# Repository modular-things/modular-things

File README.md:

# Softening Hardware with Modular-Things

use *virtualization* to easily write programs that run across multiple hardware devices

The Modular-Things project is an approach to building modular hardware systems which can be composed in software.
The underlying technology is a small networking library for packetizing and routing messages across devices ([OSAP](http://osap.tools/)) and a [web-based editor](https://modular-things.com/) for composing that hardware into functional systems in software. 

Stated simply our tools let you take hardware devices and add a library to them which allows you to plug that device into a browser-based editor where you can write programs that control it and other devices. Because it's JavaScript in the browser you can also write interfaces in HTML/CSS/JS and import various high-level libraries which interact with and control your physical computing system.

For a succinct introduction (3 min) check out our video for CHI2023 by clicking below.

An example Modular Things construction kit can be seen below with [circuits available here](https://github.com/modular-things/modular-things-circuits).

# Project Background

Modular-Things is written by [Quentin Bolsee](https://github.com/qbolsee), [Leo McElroy](https://github.com/leomcelroy) and [Jake Read](https://github.com/jakeread) based on ongoing work at the [MIT Center for Bits and Atoms](https://cba.mit.edu/) and [Hack Club](https://hackclub.com/). 

It is based on the [surprising performance of modern USB](log/2022-11_usb-motion-perf-tests-log.md), an insight that we picked up from the [urumbu project](https://gitlab.cba.mit.edu/neilg/urumbu) ([paper](https://cba.mit.edu/docs/papers/22.11.Urumbu.pdf)). Under the hood, it uses [osap](http://osap.tools/) to route packets and serialize data. Also inspired by the [virtual-machine](https://cba.mit.edu/docs/theses/16.08.Peek.pdf) architecture pioneered by [Nadya Peek](http://infosyncratic.nl/) and [Ilan Moyer](https://web.mit.edu/imoyer/www/index.html), way back in the way back. 

# Installation and Usage 

You can use the latest modular-things by navigating to [https://modular-things.com/](https://modular-things.com/), or follow these instructions to run it locally:

* install [node.js](https://nodejs.org/en/) - please use version 16.15.1 or above
* clone this repo
* run `npm install` within this repo
* run `npm run dev` to startup a local server !

### Loading Local Files

...modular-things/?file=yourFile.js&panel=devices&panelWidth=70

where file is at `repo/examples/`

--- 

# Writing New Modular-Things

For embedded (arduino) codes, install the OSAP library, which you can download as a zip here: https://github.com/jakeread/osap-arduino, and should also be available via arduino's library manager.

Also, install the `FlashStorage_SAMD` library, via the library manager.

We use the [ArduinoCore-fab-sam](https://github.com/qbolsee/ArduinoCore-fab-sam) for [these circuits](https://github.com/modular-things/modular-things-circuits), which you can install into Arduino via the notes in that repo. For the RP2040 XIAO boards, we use [Earle F. Philhower, the Third's PICO build](https://github.com/earlephilhower/arduino-pico), and for D21 XIAOs, you can follow [the XIAO docs](https://wiki.seeedstudio.com/Seeeduino-XIAO/). 

## Using the Automatic RPC

As of [`osap 0.5.0`](https://github.com/jakeread/osap-arduino/releases/tag/0.5.0), we can use an [improved design pattern](https://ekswhyzee.com/2024/02/09/no-more-newline.html) to build devices. At this time, this will only work on RP2040 based devices (which use a more modern compiler), but it is possible to back port this to c++11 based devices (most Arduinos). 

The basic pattern is pretty simple, we have a function:

```cpp
// types include float, String, int, and boolean 
float someFunction(String oneArgument, int anotherArgument){
  // ... your function body 
}
```

And we include it as a method in the devices' software object with this one-liner, handing it the function poniter, and the names of the function and its arguments: 

```cpp
OSAP_Port_RPC<decltype(&someFunction)> rpcMuleTwo(&someFunction, "someFunction", "oneArgument, anotherArgument");
```

Once we do that, and compile and load the code, the module should appear automatically when it's plugged into modular-things.com/ 

Below is a full example of a device that uses these Automatic RPCs. 

```cpp
#include <osap.h>
#include <Adafruit_GFX.h>
#include <Adafruit_SSD1306.h>

// display setup, which is wired to the XIAO's labelled SCL/SDA pins 
#define SCREEN_WIDTH 128 // OLED display width, in pixels
#define SCREEN_HEIGHT 64 // OLED display height, in pixels
#define SCREEN_ADDRESS 0x3C
Adafruit_SSD1306 display(SCREEN_WIDTH, SCREEN_HEIGHT);

// a potentiometer and a button 
// the pot is on XIAO D2/A2, which is GPIO num 28
// the button is on XIAO D3, which is GPIO num 29 (and will need a pullup)
#define PIN_POTENTIOMETER 28 
#define PIN_BUTTON 29 
#define PIN_LED_BLINK PIN_LED_R 
#define PIN_LED_WD PIN_LED_G 

// we instantiate an OSAP runtime, give it a serialport and a name: 
OSAP_Runtime osap;
OSAP_Gateway_USBSerial serLink(&Serial);
OSAP_Port_DeviceNames namePort("xylo-io-panel");

// now we want to author some functions as interfaces to our device,
// and we'll attach those as RPC's using templated OSAP_Port_RPC<> class instances 

float getPotentiometerReading(void){
  int reading = analogRead(PIN_POTENTIOMETER);
  float duty = (float)reading / 4096.0F;
  return duty; 
}

OSAP_Port_RPC<decltype(&getPotentiometerReading)> getPotRPC(&getPotentiometerReading, "getPotentiometerReading");

bool getButtonState(void){
  // we're not going to debounce anything, 
  // and our button is wired up such that it's logic high when it's not pressed, 
  // so we invert this, 
  return !(digitalRead(PIN_BUTTON));
}

OSAP_Port_RPC<decltype(&getButtonState)> rpcMuleThree(&getButtonState, "getButtonState");

uint32_t blinkOnTime = 0;

void blinkLED(void){
  // we turn an LED on and record the time, 
  // we'll check that in the loop to turn it back off, 
  // note that LEDs are wired such that logic-low is "on"
  digitalWrite(PIN_LED, LOW);
  blinkOnTime = millis();
}

OSAP_Port_RPC<decltype(&blinkLED)> rpcMuleFour(&blinkLED, "blinkLED");

void printToScreen(String message, int textSize){
  display.clearDisplay();
  display.setCursor(0, 0);
  display.setTextSize(textSize);
  display.println(message);
  display.display();
}

OSAP_Port_RPC<decltype(&printToScreen)> rpcMuleTwo(&printToScreen, "printToScreen", "message, textSize");

void newFunctionLiveDemo(int arg){
  printToScreen("you sent..." + String(arg), 3);
}

OSAP_Port_RPC<decltype(&newFunctionLiveDemo)> rpcMuleDemo(&newFunctionLiveDemo, "newFunctionLiveDemo", "intToPrint");

void setup() {
  // setup our LEDs,
  pinMode(PIN_LED_BLINK, OUTPUT);
  pinMode(PIN_LED_WD, OUTPUT);
  digitalWrite(PIN_LED_BLINK, HIGH);

  // the button needs to have a pullup
  pinMode(PIN_BUTTON, INPUT_PULLUP);
  
  // afaik, arduino sets up ADCs just by calling analogRead, 
  // and we also want to set the resolution, 
  analogReadResolution(12);
  int dummy = analogRead(PIN_POTENTIOMETER);

  // we also need to setup the display: 
  display.begin(SSD1306_SWITCHCAPVCC, SCREEN_ADDRESS);
  display.clearDisplay();
  display.display();
  display.setTextColor(SSD1306_WHITE);
  display.setTextWrap(false);

  printToScreen("bonjour", 2);

  // finally, setup OSAP,
  osap.begin();
}

const uint32_t wdInterval = 100;
uint32_t lastWd = 0;

void loop() {
  // osap runs an event loop, 
  osap.loop();

  // and we want to check in on our blinking states, 
  if(blinkOnTime){
    if(blinkOnTime + 250 < millis()){
      blinkOnTime = 0;
      digitalWrite(PIN_LED_BLINK, HIGH);
    }
  }

  // finally, we want to blink the green LED as a watchdog 
  if(lastWd + wdInterval < millis()){
    lastWd = millis();
    digitalWrite(PIN_LED_WD, !digitalRead(PIN_LED_WD));
  }
}
```

## Aligning Two Tiny Programs

To explain how module authorship works, we've just tidied up the `rgbb` example, which you can find [here (arduino)](arduino/rgbb-thing/rgbb-thing.ino) and [here (javascript)](src/lib/virtualThings/rgbb.ts).

Basically: we have an Arduino code that we give a "typeName" - that is then discovered by OSAP via the Modular-Things client. Modular-Things then looks for a matching JS or TS constructor, and if it finds one, instantiates it and passes in the devices' unique name (a string identifier). 

The constructed object can then use that string ID, as well as individual port string IDs, to route messages to its paired object. 

The result is that the "virtual thing" (javascript) acts as a proxy for the arduino-thing, making for cleaner programming model when multiple things exist in the same system. 

<table>
<tr>
  <td>
    <h2><a href="arduino/rgbb-thing/rgbb-thing.ino" target="new">Arduino "RGBB Thing"</a></h2>
  </td>
  <td>
    <h2><a href="src/lib/virtualThings/rgbb.ts" target="new">JavaScript "RGBB Thing"</a></h2>
  </td>
</tr>
<tr>
<td valign="top">

```cpp 
#include <osap.h>

// -------------------------- Define Pins for R,G and B LEDs, and one Button

#define PIN_R 14
#define PIN_G 15
#define PIN_B 16
#define PIN_BUT 17

// -------------------------- Instantiate the OSAP Runtime, 

OSAP_Runtime osap;

// -------------------------- Instantiate a link layer, 
// handing OSAP the built-in Serial object to send packetized 
// data around the network 

OSAP_Gateway_USBSerial serLink(&Serial);

// -------------------------- Adding this software-defined port 
// allows remote services to find the type-name of this device (here "rgbb")
// and to give it a unique name, that will be stored after reset 

OSAP_Port_DeviceNames namePort("rgbb");

// -------------------------- We track button state (in the loop()), 
// and we use the onButtonReq() handler (that we pass into a named port)
// to reply to messages with the provided string-name "getButtonState"

boolean lastButtonState = false;

size_t onButtonReq(uint8_t* data, size_t len, uint8_t* reply){
  // then write-into reply:
  lastButtonState ? reply[0] = 1 : reply[0] = 0;
  return 1;
}

OSAP_Port_Named getButtonState("getButtonState", onButtonReq);

// -------------------------- We can use similar structures without 
// the reply, simply recieving `data, len` on a packet to "setRGB" here 

void onRGBPacket(uint8_t* data, size_t len){
  analogWrite(PIN_R, data[0]);
  analogWrite(PIN_G, data[1]);
  analogWrite(PIN_B, data[2]);
}

OSAP_Port_Named setRGB("setRGB", onRGBPacket);

// -------------------------- Arduino Setup

void setup() {
  // startup the OSAP runtime,
  osap.begin();
  // setup our hardware... 
  analogWriteResolution(8);
  pinMode(PIN_R, OUTPUT);
  pinMode(PIN_G, OUTPUT);
  pinMode(PIN_B, OUTPUT);
  analogWrite(PIN_R, 255);
  analogWrite(PIN_G, 255);
  analogWrite(PIN_B, 255);
  // pull-down switch, high when pressed
  pinMode(PIN_BUT, INPUT);
}

// we debounce the button somewhat 

uint32_t debounceDelay = 10;
uint32_t lastButtonCheck = 0;

// -------------------------- Arduino Loop

void loop() {
  // as often as possible, we want to operate the OSAP runtime, 
  // this loop listens for messages on link-layers, and handles packets... 
  osap.loop();
  // debounce and set button states, 
  if(lastButtonCheck + debounceDelay < millis()){
    lastButtonCheck = millis();
    boolean newState = digitalRead(PIN_BUT);
    if(newState != lastButtonState){
      lastButtonState = newState;
    }
  }
}

```

</td>

<td valign="top">

```javascript
import Thing from "../../../src/lib/thing";

// the name given to us here is the "uniqueName" of the matched 
// device, we use this as a kind of address 
export default class RGBB extends Thing {
  // we can define methods that interact with the device, 
  // using the 'send' primitive, which writes data (bytes) and gets data (bytes) 
  async setRGB(r: number, g: number, b: number) {
    let datagram = new Uint8Array(3);
    datagram[0] = 255 - r * 255;
    datagram[1] = 255 - g * 255;
    datagram[2] = 255 - (b * 255) / 2;
    // to send data, we use 
    // `osap.send(name: string, targetPort: string, data: Uint8Array)`
    // ... and please use 'async' funcs with 'await' in front of 
    // network calls 
    // ... as you have probably figured out, "setRGB" here routes to 
    // the function defined around line 43 in the arduino example
    await this.send("setRGB", datagram);
  }

  async getButtonState() {
    // named-ports that return data resolve that data like-so:
    let res = await this.send("getButtonState", new Uint8Array([]));
    // and we can deserialize results... 
    if (res[0] > 0) {
      return true;
    } else {
      return false;
    }
  }

  // then we can docs our API, 
  api = [
    {
      name: "setRGB",
      args: [
        "red: 0 to 1",
        "green: 0 to 1",
        "blue: 0 to 1"
      ],
    },
    {
      name: "getButtonState",
      args: [],
      return: "0 or 1"
    }
  ]
}
```

</td>
</tr>
</table>

> At the time of writing, we mostly write modular-things using SAMD21 and RP2040 platforms. It is likely that OSAP will run on other microcontrollers, but there are funky-things that happen with Arduino's internal abstractions of i.e. `Serial` objects (which OSAP uses to button up link layers) and Flash-Storage libraries (to store names). Drop us a line if you have a favourite platform that you would like to see supported.

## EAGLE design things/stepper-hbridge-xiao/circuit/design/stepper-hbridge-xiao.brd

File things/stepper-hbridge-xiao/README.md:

---
author: Jake Read
name: stepper-hbridge-xiao
schematic: circuit/images/schematic.png
layout: circuit/images/layout.png
preview: circuit/images/preview.png
# fabbed: 
---
## H-Bridge Stepper

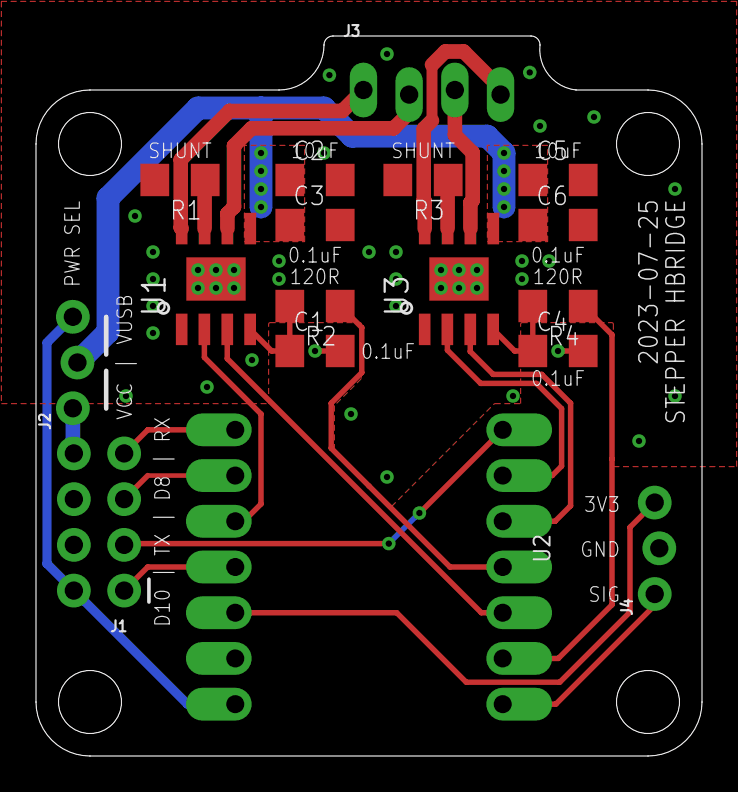
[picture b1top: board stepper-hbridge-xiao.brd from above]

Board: 2 copper layers, 37.0 x 40.0 mm, 17 parts (0 on the bottom side), 24 nets.

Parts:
C1, C4: 0.1uF; 1206
C2, C5: 1uF; 1206
C3, C6: 10uF; 1206
J1: CONN_2X4LOCK; 2X4-LOCK
J2, J4: 1X03_LOCK_NO_SILK
J3: CONN_04SCREW_TERM; 1X04_SCREW-TERM
R1, R3: 300mOhm; 1206
R2, R4: 120R; 1206
U1, U3: A4950; SOIC8_PAD
U2: MOUDLE14P-2.54-21X17.8MM

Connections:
+3V3: J4.3, U2.12
+5V: J1.2, J2.3, U2.14
AIN1: U2.5, U3.3
AIN2: U2.6, U3.2
AVREF: R4.1, U2.2
BIN1: U1.3, U2.3
BIN2: U1.2, U2.10
BP_VCC: J1.8, J2.1
BVREF: R2.1, U2.4
B_D8: J1.5, U2.9
B_D10: J1.1, U2.11
B_RX: J1.7, U2.8
B_TX: J1.3, U2.7
GND: C1.2, C2.2, C3.2, C4.2, C5.2, C6.2, J1.4, J1.6, J4.2, R1.2, R3.2, U1.1, U1.P$1, U2.13, U3.1, U3.P$1
LIMIT: J4.1, U2.1
LSSA: R3.1, U3.7
LSSB: R1.1, U1.7
unnamed: C1.1, R2.2, U1.4
unnamed: C4.1, R4.2, U3.4
OA1: J3.3, U3.6
OA2: J3.4, U3.8
OB1: J3.2, U1.6
OB2: J3.1, U1.8
VCC: C2.1, C3.1, C5.1, C6.1, J2.2, U1.5, U3.5

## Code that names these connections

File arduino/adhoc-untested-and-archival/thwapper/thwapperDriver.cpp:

/*
thwapperDriver.cpp

thwapper code for two A4950s w/ VREF via TC -> RC Filters 

Jake Read at the Center for Bits and Atoms
(c) Massachusetts Institute of Technology 2022

This work may be reproduced, modified, distributed, performed, and
displayed for any purpose, but must acknowledge the squidworks and ponyo
projects. Copyright is retained and must be preserved. The work is provided as
is; no warranty is provided, and users accept all liability.
*/

#include "thwapperDriver.h"

// h-bridge pins, rendered per actual D21 GPIO 

/*
PIN   | XIAO  | XIAO:D21  | D21 TC    |
--------------------------|
APWM  | 2     | PA04      | TCC0:0(E) |
AIN1  | 5     | PA08      |
AIN2  | 6     | PA09      |
BPWM  | 4     | PA11      | TCC0:3(F) |
BIN1  | 3     | PA10      |
BIN2  | 10    | PA05      |
*/

#define APWM_PIN 4
#define AIN1_PIN 8
#define AIN2_PIN 9
#define BPWM_PIN 11
#define BIN1_PIN 10
#define BIN2_PIN 5

// pin masks / ports / fundamental ops 

#define AIN1_PORT PORT->Group[0]
#define AIN2_PORT PORT->Group[0]
#define BIN1_PORT PORT->Group[0]
#define BIN2_PORT PORT->Group[0] 
#define AIN1_BM (uint32_t)(1 << AIN1_PIN)
#define AIN2_BM (uint32_t)(1 << AIN2_PIN)
#define BIN1_BM (uint32_t)(1 << BIN1_PIN)
#define BIN2_BM (uint32_t)(1 << BIN2_PIN)
// on TCC0-6 (F) or TCC2-0 (E)
#define APWM_PORT PORT->Group[0] 
#define APWM_BM (uint32_t)(1 << APWM_PIN)
// on TCC0-0 (E)
#define BPWM_PORT PORT->Group[0] 
#define BPWM_BM (uint32_t)(1 << BPWM_PIN) 

#define AIN1_HI AIN1_PORT.OUTSET.reg = AIN1_BM
#define AIN1_LO AIN1_PORT.OUTCLR.reg = AIN1_BM
#define AIN2_HI AIN2_PORT.OUTSET.reg = AIN2_BM
#define AIN2_LO AIN2_PORT.OUTCLR.reg = AIN2_BM 
#define BIN1_HI BIN1_PORT.OUTSET.reg = BIN1_BM
#define BIN1_LO BIN1_PORT.OUTCLR.reg = BIN1_BM
#define BIN2_HI BIN2_PORT.OUTSET.reg = BIN2_BM
#define BIN2_LO BIN2_PORT.OUTCLR.reg = BIN2_BM

// h-bridge atomic ops: a/b channels up/down/off (fast decay) 

#define A_UP AIN2_LO; AIN1_HI
#define A_OFF AIN2_LO; AIN1_LO
#define A_DOWN AIN1_LO; AIN2_HI
#define B_UP BIN2_LO; BIN1_HI 
#define B_OFF BIN2_LO; BIN1_LO
#define B_DOWN BIN1_LO; BIN2_HI

void thwapper_begin(void){
  // -------------------------------------------- DIR PINS 
  // all of 'em, outputs 
  AIN1_PORT.DIRSET.reg = AIN1_BM;
  AIN2_PORT.DIRSET.reg = AIN2_BM;
  BIN1_PORT.DIRSET.reg = BIN1_BM;
  BIN2_PORT.DIRSET.reg = BIN2_BM;
  // -------------------------------------------- TCC SETUPS 
  // s/o https://blog.thea.codes/phase-shifted-pwm-on-samd/ 
  // unmask the peripheral, 
  PM->APBCMASK.reg |= PM_APBCMASK_TCC0 | PM_APBCMASK_TCC1 | PM_APBCMASK_TCC2;
  // make a clock w/ DFLL48 src on ch4;
  GCLK->GENCTRL.reg = GCLK_GENCTRL_ID(4)|
                      GCLK_GENCTRL_GENEN |
                      GCLK_GENCTRL_SRC_DFLL48M |
                      GCLK_GENCTRL_IDC;
  while(GCLK->STATUS.bit.SYNCBUSY);
  // route this clk (on 4) to our peripheral 
  GCLK->CLKCTRL.reg = GCLK_CLKCTRL_CLKEN |       // enable a clock, 
                      GCLK_CLKCTRL_GEN_GCLK4 |   // select 
                      GCLK_CLKCTRL_ID_TCC0_TCC1; // route to TCC0 / TCC1 
  while(GCLK->STATUS.bit.SYNCBUSY);
    // route this clk (on 4) to our peripheral 
  GCLK->CLKCTRL.reg = GCLK_CLKCTRL_CLKEN |       // enable a clock, 
                      GCLK_CLKCTRL_GEN_GCLK4 |   // select 
                      GCLK_CLKCTRL_ID_TCC2_TC3; // route to TCC0 / TCC1 
  while(GCLK->STATUS.bit.SYNCBUSY);
  // -------------------------------------------- PWM Generating TCC's
  /*
  APWM  | 2     | PA04      | TCC0:0(E) |
  BPWM  | 4     | PA11      | TCC0:3(F) |
  */
  // set pin as output, 
  APWM_PORT.DIRSET.reg = APWM_BM;
  // mux APWM (PA04: even) onto E peripheral 
  APWM_PORT.PINCFG[APWM_PIN].reg |= PORT_PINCFG_PMUXEN;
  APWM_PORT.PMUX[APWM_PIN >> 1].reg = PORT_PMUX_PMUXE_E; 
  // mux BPWM (PA11: odd) onto F peripheral 
  BPWM_PORT.PINCFG[BPWM_PIN].reg |= PORT_PINCFG_PMUXEN;
  BPWM_PORT.PMUX[BPWM_PIN >> 1].reg = PORT_PMUX_PMUXO_F;
  // TCC0 settings
  TCC0->CTRLA.reg |= TCC_CTRLA_PRESCALER_DIV1; 
  TCC0->WAVE.reg = TCC_WAVE_WAVEGEN_NPWM;
  while(TCC0->SYNCBUSY.bit.WAVE);
  TCC0->PER.reg = 256; 
  while(TCC0->SYNCBUSY.bit.PER);
  TCC0->CCB[0].reg = 0;   // APWM init w/ no juice 
  TCC0->CCB[3].reg = 0;   // BPWM ||
  TCC0->CTRLA.bit.ENABLE = 1;
}

// current [-255:255] 
void thwapper_a_write_current(int16_t current){
  if(current > 0){
    if(current > 255) current = 255;
    A_UP;
    TCC0->CCB[0].reg = current;
  } else if (current < 0){
    if(current < -255) current = -255;
    A_DOWN;
    TCC0->CCB[0].reg = current;
  } else {
    A_OFF;
    TCC0->CCB[0].reg = 0;
  }
}

// current [-255:255]
void thwapper_b_write_current(int16_t current){
  if(current > 0){
    if(current > 255) current = 255;
    B_UP;
    TCC0->CCB[3].reg = current;
  } else if (current < 0){
    if(current < -255) current = -255;
    B_DOWN;
    TCC0->CCB[3].reg = current;
  } else {
    B_OFF;
    TCC0->CCB[3].reg = 0;
  }
}

// some stateful thwap tracking,

uint32_t strike_time_ms = 50;
uint32_t strike_start_a = 0;
boolean strike_ongoing_a = false;

// use velocity is current, strike timing always the same... 
void thwapper_a_strike(uint8_t velocity){
  thwapper_a_write_current(velocity);
  strike_start_a = millis();
  strike_ongoing_a = true;
}

// loop to update sinusoids out or async cancel thwaps... 
void thwapper_loop(void){
  if(strike_ongoing_a){
    if(strike_start_a + strike_time_ms < millis()){
      strike_ongoing_a = false; 
      thwapper_a_write_current(0);
    }
  }
}

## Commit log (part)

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2022-12-17 squish video
2022-12-17 last tiny editos
2022-12-17 await setname"
2022-12-18 shift some mvc codes in osapjs
2022-12-18 arduino codes for osap 0.0.1
2022-12-19 Websocket example
2022-12-19 websocket client
2022-12-20 2.30 and 34.30 fixed points in use, but needs stopDistanace up-front maths
2022-12-21 fixed point w/ no-division stopping-check calc seems OK, but accel scaling is whack
2022-12-21 scaling on internal calcs, and 2nd-order time scaling for accel vals
2023-01-04 Add start of nextjs app
2023-01-04 Add more of client functionality in client-next
2023-01-05 Implement more functionality in client-next
2023-01-05 client-next (hopefully, can't test everything) reaches feature parity with old mt-tool
2023-01-06 Add file tree
2023-01-06 Add some documentation to client-next's structure
2023-01-06 typo
2023-01-07 fix hydration error/a11y
2023-01-07 better placeholder/icon sizing
2023-01-07 Add device renaming
2023-01-07 CM tabs support + load/save state
2023-01-09 Initial webserial impl
2023-01-09 Add more webserial
2023-01-09 Modules
2023-01-09 web serial improvements
2023-01-10 Add github action for deployment
2023-01-10 move github action
2023-01-10 Set gh action working dir
2023-01-10 fix working directory for detect package manager
2023-01-10 fix upload artifact working dir
2023-01-10 fix favicon
2023-01-10 fix next setup
2023-01-12 Auto save to localstorage, help tab, font, minor improvements
2023-01-12 Fix next basepath
2023-01-12 correct bad -ve action w/ one abs()
2023-01-12 done with fixed point arithmetic
2023-01-13 Help panel, improved hooked settimeout/setinterval, full page view
2023-01-13 Add missing key shortcut
2023-01-15 xiao rp2040 PID
2023-01-25 Added more firmware
2023-02-01 init client astro
2023-02-01 WIP client-astro
2023-02-01 fixed up help markdown styles a bit
2023-02-01 removing other clients
2023-02-01 changing panel default to devices
2023-02-01 remove client directory
2023-02-01 added examples
2023-02-01 added github logo
2023-02-01 moved samples
2023-02-01 minor style changes
2023-02-01 added notes TODO and console mention in help
2023-02-01 added script bundling back in
2023-02-01 added url import example
2023-02-03 Add Web Serial API Warning
2023-02-06 added disconnect all button
2023-02-06 add redundant close calls
2023-02-10 added example machine interface
2023-02-10 added file loading
2023-02-10 added color seperation
2023-02-12 fix rgbb callback
2023-02-18 first pass at rpc, rolls up w/o arg name, osap 0.2.1
2023-02-18 add rpc code example, auto rollup works and reports APIs
2023-02-23 fix synchronizer example
2023-02-25 added thing state setter
2023-04-10 Functioning console
2023-04-18 correct pinouts on rp2040 stepper
2023-04-19 big old osap update
2023-04-19 webserial cobs link in its own box ... working on cute lil update handlers
2023-04-19 some link-insertion at old-empty-ports... and looking at upate schedules
2023-04-19 re-worked disconnect-all, learned some webserial fkery
2023-04-19 one more disconnect bug
2023-04-20 renames doubles
2023-04-20 with new rgbb... works great
2023-04-20 all the basics work, cleanup, clarifications and testing needed
2023-04-20 coupla tiny... comments ?
2023-04-20 removing deadies and re-writing names
2023-04-20 actual flowcontrol-ish in the cobs-thing
2023-04-20 updating virtual things
2023-04-20 updated things to new osap
2023-04-21 added haxidraw interface
2023-04-21 update rgbb
2023-04-21 updated firmwares
2023-04-21 new example
2023-04-21 notes on strange time-of-flight bug
2023-04-21 stepper looks good
2023-04-21 synchronizer works same-as-prior, and seems all-good with new stepper
2023-04-21 update haxidraw control
2023-04-22 match rgbb and potentiometer to osap examples
2023-04-22 author new how-to-make-new-things section
2023-04-22 table format
2023-04-22 rm sneaky h2
2023-04-22 rescan... actually rescans
2023-04-27 cleanup osapjs headers
2023-04-28 Make file url work in production
2023-04-28 Use relative paths unless in production
2023-05-10 adds checksums to name-writes, fixes shorty-names bug with osap 0.4.4
2023-05-18 fix installation and usage notes
2023-06-28 start maxl dev baby
2023-06-28 split files, embedded stub compiles
2023-06-28 embedded glue code
2023-06-29 maxl to /maxl in vt, tidy, start to test
2023-06-29 hello trajectory eating world, things are re-factored - now into queue objectification, delivery, etc
2023-06-29 add panel choice and panel width options to url
2023-06-29 ok, going to move to time-based queue mgmgt
2023-06-29 moves through a test queue OK
2023-06-29 maxl does time-estimation step
2023-06-29 barebones / dead ez halt for jogs, limits...
2023-06-30 found some dispatching bugs, fixed - two motor maxl-ing now
2023-07-01 STASH before individual-track maxl
2023-07-01 hello-world on two motors with separated position tracks
2023-07-01 chunking embedded funcking begins
2023-07-02 bust MAXL into TRAXLs
2023-07-02 decouple continues, emergency stash...
2023-07-06 working on maxl, side quest to add messageEscape debug port type
2023-07-06 ok for one test
2023-07-06 two-motor test code is OK, next steps are more track types and real config style
2023-07-15 uses config settings to subscribe, transmit, still only motion tracks though
2023-07-15 clean .gitignored-vscode arduino configs
2023-07-19 one axis home on accel demo
2023-07-19 homes and comes off OK
2023-07-19 stash b4 queue rewerk
2023-07-19 aprex fix-la the queueing bugs (we think)
2023-07-19 quick dev for pipes-up thru osap, now reading accels...
2023-07-20 finish time-sync'd accel thing, starting neopixel thing
2023-07-20 proto bitmap reader
2023-07-20 slipshod event-channel datagram authorship
2023-07-20 event track READER
2023-07-20 hello world via light painting
2023-07-26 stash with working minimal example
2023-07-26 redux for stepper motor, using memcpy deserialize
2023-07-26 lights and motion sync'd once again, a little cleaner this time
2023-08-03 roll decent pid loop on the bed heater
2023-08-08 quick haxi sketch 4 rob and leo
2023-08-08 rm console commandeering, add example rob code
2023-08-14 refactor heater code into heater-code-class
2023-08-14 bed heater and its partner are werken
2023-08-17 bed heater improves, hotend heater alive, found circuit bug in hotend-loadcell
2023-08-24 start haxiboard dev, swap maxl 'actu' to 'device' and 'reader' to 'listener'
2023-08-24 haxi board does motion things
2023-08-24 haxiboard gets a servo listener
2023-08-24 haxi proper spu, test paths
2023-08-25 add a few test files, more test paths, and do auto-scale and auto-onto-bed for svg in machine-interface
2023-08-31 sort older examples, found a bug in the transforms code
2023-08-31 maxl passes the rhino test, on the haxidraw
2023-09-06 stash before a tidy
2023-09-06 interstitial cleanup commit...
2023-09-06 ... log
2023-09-06 rename haxithing sync interf
2023-09-06 manuel merge from music-things, stashing thwappers and hubs in adhoc
2023-09-06 some cleanup and comprehension with leo
2023-09-06 rm the log
2023-09-09 expose the limit switch in the non-syncd stepper
2023-09-13 adding time-sync updates to the maxl-stepper
2023-09-24 moved things to slash-things
2023-09-24 shuffle circuits and arduino codes into things-folder
2023-09-24 template readmes
2023-11-03 add backpack spec-ish and example template
2023-11-08 towards more-better circuit docs and folder spec etc
2023-11-08 larger svg in markdown
2023-11-09 folder structure notes
2023-11-09 add dist to ignore in case of local npm-build-then-push mistake"
2023-11-09 figured some sht out
2023-11-17 add notes
2023-11-19 working on things page
2023-11-19 statically generating circuit pages
2023-11-22 tidy unstable-and-old as such
2023-11-22 cleanupt some, bring rgbb back, prep for new class...
2023-11-22 looks like new-constructor-pattern works, its free real estate
2023-11-22 tidy and note rgbb.ts example in readme
2023-11-22 touchup stepper
2023-11-22 stabilize rgbb, stepper, mosfet and servo on new inheritance
2023-11-27 start one-axis example stub
2023-11-27 peel off upgrades
2023-11-27 setup debugs and unfk schema, img for stepper
2023-11-27 new lutgen for halfwave, fill out high perf resolution for steppage
2023-11-27 spacing in servo.ts and fixed-p stepper_point
2023-11-27 cleanup!
2023-11-28 resolve fixed point and multi-tick commutation, no guards on FP overflows yet
2023-11-28 added guards on fixedp arithmetic
2023-11-28 use fixedp64 to avoid position overflows
2023-11-28 reconfig _global
2023-11-28 fixed point position, vel modes should work, testing next
2023-11-29 sys tests OK
2023-11-29 cleanup, tests still OK
2023-11-29 re-interfaced
2023-11-29 stabilize motor fw, one dof limit example is OK
2023-11-29 sync to match motors, motion-upgrades complete
2023-11-29 unfk-d some API notes for moteur
2023-11-30 rename things for gallery WIP
2023-11-30 things gallery
2023-11-30 add links to images
2023-11-30 added code snippets
2023-11-30 firmware progress
2023-12-01 apres machine-week-recitation-two
2023-12-01 xiao firmware
2023-12-01 todo notes
2023-12-01 tidy TODO
2023-12-01 tidy _things.json, flatten unstable-things
2023-12-01 cleanup /things menus, links, etc
2023-12-01 rel href fkery
2023-12-01 thing page title
2023-12-03 servo fix
2023-12-06 velocity-near-zero statemachine bug fix
2023-12-12 small note on URL args
2024-02-05 just some todos
2024-02-05 proto rpc port
2024-02-05 tuple candidate
2024-02-06 towards that rpc... starting in on js caller impl
2024-02-07 candidate working auto-rpc, missing lots of handles and maybe stack overflowing
2024-02-08 rollup OK on one function, one mule...
2024-02-08 can compile now across ret-args, void-args, ret-void, and void-void functions
2024-02-09 mostly done specializing etc for void-void, void-args, ret-args, ret-void etc, just need to specialize constructor
2024-02-09 no-args cpp constructor defers to main, and some tidy in ts
2024-02-10 it's the xylo-panel example, yall
2024-02-13 state after recording osap 0.5.0 update
2024-02-13 modify the readme for the auto RPC
2024-02-13 try move to modular-things.com
2024-02-20 try to fix slash-things rel link
